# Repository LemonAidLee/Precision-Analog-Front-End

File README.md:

# Precision Mixed-Signal Data Acquisition Front End (AFE)

A four-stage precision analog front end that conditions a ±100 mV bipolar sensor signal into the 0–3.3 V unipolar window of a 16-bit ADS1115 ADC, designed for an ESP32-WROOM-32 host. Designed, simulated in LTspice, and laid out in KiCad. **Not built — no physical hardware exists.**

*Rev A board (78 mm × 100 mm, 2-layer), KiCad 3D render. The physical board has not been manufactured.*

---

## Overview

A sensor that outputs a few tens of millivolts, swinging both positive and negative, cannot be connected to a single-supply ADC. It is too small to use the converter's resolution, it goes below the converter's ground rail, and it carries out-of-band content the converter will alias.

This project is the hardware that sits between the two: an analog front end that band-limits, amplifies, and re-centres the signal so that a 16-bit ADC sees a well-conditioned, in-range voltage, and an ESP32 can read it over I²C.

| | |
|---|---|
| **Input** | ±100 mV bipolar, single-ended (J1) |
| **Output** | 0.31 V … 2.96 V unipolar, centred on VREF (to ADS1115 A0) |
| **Overall gain** | 13.25 V/V (22.4 dB) |
| **Bandwidth** | 2nd-order Butterworth low-pass, f₀ = 1.06 kHz |
| **Analog supply** | ±15 V (unregulated), external via screw terminal (J2); regulated on-board to ±12 V by LM7812 / LM7912 |
| **Digital supply** | 3.3 V from the ESP32 module's on-board regulator |
| **Op-amps** | 2 × TL082 (dual JFET-input), DIP-8 |
| **ADC** | ADS1115 breakout, 16-bit, I²C, ±4.096 V FSR |
| **Board** | 78 mm × 100 mm, 2-layer, 1.6 mm, all through-hole |
| **Status** | Designed · Simulated (DC) · Schematic complete · PCB fully routed with GND pour |

---

## Engineering motivation

Connecting a low-level sensor directly to a microcontroller ADC fails for four independent reasons, and each one needs its own circuit stage:

| Problem | Consequence | Stage that solves it |
|---|---|---|
| Signal is out-of-band above ~1 kHz | High-frequency interference folds back into the measurement band | Stage 1 — Sallen-Key low-pass |
| Signal is ~100 mV into a 4.096 V converter span | Only ~2.4 % of the ADC range is used; quantisation noise dominates | Stage 2 — ×10 gain |
| Signal is bipolar; the ADC ground rail is 0 V | Negative half-cycles are clipped or damage the input | Stage 3 — inverting summing level shift onto VREF |
| The summing stage inverts the signal | Polarity is wrong at the ADC | Stage 4 — unity-gain inverter |

Doing all four in one stage is possible but couples the design decisions together — the gain would set the filter Q, the offset would move with gain, and nothing could be probed independently. Splitting them keeps every design equation independent and gives four testable nodes.

---

## Signal flow

```
                 ±100 mV                  ±159 mV               ±1.59 V
   SENSOR ──▶ ┌───────────┐  VFILTER  ┌───────────┐  VAMP  ┌──────────────┐
   J1         │  STAGE 1  │ ────────▶ │  STAGE 2  │ ─────▶ │   STAGE 3    │
              │ Sallen-Key│           │ Non-inv.  │        │  Inverting   │
              │  LPF ×1.59│           │  amp ×10  │        │  summer      │
              │  U1A      │           │  U1B      │        │  U2A         │
              └───────────┘           └───────────┘        └──────┬───────┘
                                                                  │ VX
                        +3.3 V                                    │ −2.96 … −0.31 V
                          │                                       ▼
                     ┌────┴────┐  VREF = 1.637 V           ┌──────────────┐
                     │ 470/470 │ ─────────────────────────▶│   STAGE 4    │
                     │ divider │                           │ Unity inv.   │
                     │ + 100 nF│                           │  U2B         │
                     └─────────┘                           └──────┬───────┘
                                                                  │ VADC
                                                                  │ 0.31 … 2.96 V
                                                                  ▼
                                                        ┌────────────────────┐
                                                        │ ADS1115  (A0)      │
                                                        │ 16-bit, ±4.096 V   │
                                                        └─────────┬──────────┘
                                                                  │ I²C (SDA/SCL)
                                                                  ▼
                                                        ┌────────────────────┐
                                                        │ ESP32-WROOM-32     │
                                                        └────────────────────┘
```

Full node-by-node breakdown: **[03 — Signal Path](docs/03_Signal_Path.md)**

---

## Key specifications

| Parameter | Design value | Source |
|---|---|---|
| Input range | ±100 mV | Design target (silkscreened on board) |
| Stage 1 passband gain, K | 1 + 5.9k/10k = **1.590** | Calculated, LTspice-confirmed |
| Stage 1 cutoff, f₀ | 1/(2π·1.5k·100n) = **1061 Hz** | Calculated |
| Stage 1 Q | 1/(3 − K) = **0.709** (Butterworth ≈ 0.707) | Calculated |
| Stage 2 gain | 1 + 90k/10k = **10.00** | Calculated, LTspice-confirmed |
| Stage 3 signal gain | −30k/36k = **−0.8333** | Calculated, LTspice-confirmed |
| Stage 3 reference gain | −30k/30k = **−1.000** | Calculated |
| Stage 4 gain | −10k/10k = **−1.000** | Calculated |
| **Total gain, VSENSOR → VADC** | **13.25 V/V** | LTspice: 13.248 V/V |
| VREF (unloaded) | 3.3 × 470/940 = **1.650 V** | Calculated |
| VREF (loaded by Rref1) | **1.637 V** | LTspice: 1.6372 V |
| VADC at −100 mV / 0 / +100 mV | 0.313 / 1.637 / 2.962 V | LTspice (TL082) |
| ADC resolution referred to input | 4.096 V / 2¹⁵ / 13.25 = **9.4 µV/LSB** | Calculated |

---

## Hardware architecture

**Analog section** (left half of the board) — two TL082 dual op-amps in DIP-8 provide the four amplifier stages. All resistors are 1/4 W axial through-hole on a 10.16 mm pitch, arranged in a single labelled column so every feedback network can be identified and swapped without a schematic in hand. Analog supplies enter on a 3-pin 5 mm screw terminal (+15V_RAW / GND / −15V_RAW) from an external bench supply; on-board **LM7812 / LM7912 linear regulators** (U3/U4, with C4–C7 input/output bypass) clean this to the ±12 V the op-amps actually run on. The raw rail needs headroom above 12 V for the regulators to hold regulation, which is why the connector is no longer labelled ±12 V directly.

**Digital section** (right half) — the ESP32 dev board seats in two 1×19 pin sockets and supplies 3.3 V from its own regulator; the ADS1115 breakout seats in a 1×10 socket above it. The two sections meet only at the VADC trace and the shared ground.

Details: **[07 — KiCad Schematic and PCB](docs/07_KiCad_Schematic_and_PCB.md)**

---

## Simulation

Design verification was done in LTspice in two phases.

**Phase 1 — stage development with OP1177.** Each stage was designed, simulated, and iterated on its own bench: the Sallen-Key filter (AC sweep + transient), the ×10 gain stage (AC + transient), the level shifter, and then a two-stage and finally a four-stage integration. This phase used the OP1177 model that ships with LTspice, and produced the resistor values now in the schematic.

**Phase 2 — TL082 substitution.** The physical build targets TL082, so a third-party TL082 PSpice macromodel (`TL082.lib`) was brought in and the full chain re-run against it. The DC transfer at −100 mV / 0 / +100 mV was extracted and matches the ideal transfer function to within 0.02 %.

*Four-stage chain as simulated with the TL082 macromodel.*

| Test condition | Ideal (calculated) | LTspice, TL082 | Δ |
|---|---:|---:|---:|
| VSENSOR = 0 | 1.637 V | 1.63737 V | +0.4 mV |
| VSENSOR = +100 mV | 2.962 V | 2.96220 V | +0.2 mV |
| VSENSOR = −100 mV | 0.313 V | 0.31254 V | −0.2 mV |

**Two simulation issues are open and are not hidden here:** the TL082 build's filter section is wired as a passive two-pole RC rather than the Sallen-Key that is in the KiCad schematic (DC results unaffected, AC results not representative), and the OP1177 reference file no longer runs. Both are documented in **[05 — LTspice Simulation](docs/05_LTspice_Simulation.md)**.

Full detail: **[05 — LTspice Simulation](docs/05_LTspice_Simulation.md)** · **[06 — Simulation Results](docs/06_Simulation_Results.md)**

---

## PCB design

*F.Cu (red), B.Cu (blue — mostly the GND pour), silkscreen and board outline. Fully routed.*

- **78.1 mm × 99.6 mm** bounding box (2 layers, 1.6 mm FR4)
- 29 footprints, all through-hole; 115 pads
- 209 track segments (112 on F.Cu, 97 on B.Cu), ≈1355 mm total; 10 vias (0.6 mm / 0.3 mm drill)
- **GND poured on both F.Cu and B.Cu** (2 zones, 0.25 mm min thickness)
- Design rules: 0.2 mm min clearance, 0.2 mm min track, 0.5 mm copper-to-edge
- **DRC: 0 violations.** **ERC: 0 errors, 32 warnings** (all "label connected to only one pin" — the unused ESP32 GPIO breakout labels)
- No test points; no local decoupling at the op-amp supply pins

**Routing is complete.** Every net — including the seven internal analog nodes (the two filter nodes and the five op-amp inverting-input/feedback nodes) that an earlier netlist-sync bug had left with no copper — now has a fully routed connection, plus a GND pour on both layers. See **[07 — KiCad Schematic and PCB](docs/07_KiCad_Schematic_and_PCB.md)** for the routing table and the story of that bug.

---

## ESP32 + ADS1115 interface

The digital side is a **hardware interface only — no firmware has been written.**

| ADS1115 (J5) | Net | Goes to |
|---|---|---|
| 1 VDD | +3V3 | J3-1 (ESP32 3V3) |
| 2 GND | GND | Board ground |
| 3 SCL | SCL | J4-3 (ESP32 GPIO22) |
| 4 SDA | SDA | J4-6 (ESP32 GPIO21) |
| 5 ADDR | GND | Sets I²C address 0x48 |
| 6 ALRT | — | Not connected |
| 7 A0 | **VADC** | Stage 4 output |
| 8–10 A1–A3 | — | Not connected |

Details: **[09 — ESP32 + ADS1115 Interface](docs/09_ESP32_ADS1115_Interface.md)**

---

## Verification status

| Item | Designed | Simulated | On PCB | Routed | Physically tested |
|---|:--:|:--:|:--:|:--:|:--:|
| Sallen-Key low-pass (U1A) | ✓ | ✓ (AC/transient, OP1177 · DC only, TL082) | ✓ | ✓ | — |
| ×10 gain stage (U1B) | ✓ | ✓ (AC/transient, OP1177 · DC, TL082) | ✓ | ✓ | — |
| Level shifter (U2A) | ✓ | ✓ (DC, TL082) | ✓ | ✓ | — |
| Unity inverter (U2B) | ✓ | ✓ (DC, TL082) | ✓ | ✓ | — |
| 1.65 V reference divider | ✓ | ✓ (DC, TL082, incl. loading) | ✓ | ✓ | — |
| ADS1115 interface | ✓ | — | ✓ | ✓ | — |
| ESP32 interface | ✓ | — | ✓ | ✓ | — |
| ±12 V regulation (LM7812/LM7912) | ✓ | ideal sources only in signal-chain sims | ✓ | ✓ | — |
| Firmware | — | — | — | — | — |

**No physical prototype exists.** The board has not been fabricated, assembled, powered, or measured. Every performance figure in this repository is either a hand calculation or an LTspice result. Physical hardware validation is outside the current project scope.

---

## Engineering challenges

- **Choosing K = 1.59 rather than "gain = 1".** In an equal-component Sallen-Key, the passband gain and the pole Q are the same knob: Q = 1/(3 − K). A unity-gain buffer would give Q = 0.5 (overdamped, soft knee). K = 1.586 is the value that lands Q on 0.7071 — maximally flat. The 5.9 kΩ / 10 kΩ pair gives K = 1.590 and Q = 0.709, 0.3 % from ideal, using stock values.
- **Sizing the level shifter so the extremes stay inside the rail, not just the centre.** An earlier iteration used Rin1 = 20 kΩ. That still centred on 1.65 V at zero input, but the ±100 mV extremes landed at −0.74 V and +4.03 V — outside the ADC's supply rails in both directions. Rin1 = 36 kΩ trades gain for headroom and puts the extremes at 0.31 V / 2.96 V.
- **Predicting the reference divider's error before simulating it.** VREF is not 1.650 V in circuit; Rref1 (30 kΩ) sinks ~55 µA from a 235 Ω source, pulling it to 1.637 V. That 13 mV shift is a fixed offset the firmware can calibrate out — but it had to be identified as a systematic error rather than mistaken for simulation noise.
- **Migrating from a model that exists to a part that can be bought.** OP1177 has a vendor-supplied LTspice model; TL082 does not ship with LTspice. Getting the TL082 macromodel to converge required source stepping, and re-running the chain surfaced the fact that the two integration files had drifted apart.

---

## Current project status

**Designed · Simulated · Schematic complete · PCB placed and fully routed with a GND pour · Documented.**

Not manufactured, not assembled, not physically validated, not production-ready.

---

## Limitations

- No physical prototype; no oscilloscope, multimeter, or spectrum measurements of any kind.
- No local supply decoupling at the TL082 pins, no test points on the current board.
- ±12 V is regulated on-board (LM7812/LM7912), but the input rail is still an external, unregulated ±15 V supply — there is no AC-mains or USB-derived path to that rail.
- The TL082 full-chain simulation covers **DC only**; there is no AC or transient run against the TL082 model, and its filter section does not match the board.
- The AC and transient results in this repository were produced with **OP1177**, not the TL082 that is on the schematic.
- The 1.06 kHz filter corner sits above the ADS1115's 430 Hz Nyquist frequency at its 860 SPS maximum rate — it band-limits the signal but does not anti-alias the converter.
- No input protection, no reverse-polarity protection, no sensor characterisation.
- No firmware.

---

## Future improvements

1. Resolve the two open simulation discrepancies (filter topology in the TL082 file; repair the OP1177 reference bench).
2. Run AC and transient sweeps against the TL082 model and compare to the OP1177 reference.
3. Add 100 nF decoupling at each TL082 supply pin, and test points at VSENSOR / VFILTER / VAMP / VREF / VADC.
4. Fabricate and assemble; bring up the rails before the signal chain.
5. Measure DC transfer, frequency response, and noise floor; compare against simulation.
6. Write ESP32 firmware: I²C driver for the ADS1115, offset/gain calibration, data logging.
7. Revise to Rev B against measured data.

**Done since the last revision of this document:** PCB routing is complete (including seven internal analog nets a netlist-sync bug had silently left unrouted — see [07 §5](docs/07_KiCad_Schematic_and_PCB.md#5-resolution--the-unrouted-nets-and-the-bug-behind-them)), a GND pour was added on both copper layers, and on-board LM7812/LM7912 regulation replaced the external-±12V-only supply architecture.

---

## Repository structure

```
.
├── README.md                     ← this file
├── docs/                         ← full engineering documentation
│   ├── README.md                 ← documentation index
│   ├── 01_Project_Overview.md
│   ├── 02_System_Architecture.md
│   ├── 03_Signal_Path.md
│   ├── 04_Analog_Circuit_Design.md
│   ├── 05_LTspice_Simulation.md
│   ├── 06_Simulation_Results.md
│   ├── 07_KiCad_Schematic_and_PCB.md
│   ├── 08_Components_and_BOM.md
│   ├── 09_ESP32_ADS1115_Interface.md
│   ├── 10_Engineering_Decision.md
│   ├── Portfolio_Summary.md      ← recruiter-facing summary
│   ├── images/                   ← schematic, PCB and LTspice figures
│   └── design_files/             ← generated PDF / BOM exports + source pointers
├── KiCAD_PCB_Design/             ← KiCad 10 project (schematic, PCB, STEP)
├── LTSpice_Simulation/           ← LTspice schematics, netlists, TL082 model
└── Precision DAQ AFE_Documentation/   ← original engineering log / working notes
```

---

## Skills demonstrated

**Analog design** — active filter synthesis (Sallen-Key, Butterworth Q targeting), op-amp gain-stage design, inverting summing amplifiers, level shifting, resistive reference design with loading analysis, supply-rail headroom budgeting.

**Simulation** — LTspice AC / transient / DC-sweep analysis, third-party SPICE macromodel integration, convergence troubleshooting (Gmin and source stepping), model-substitution verification, netlist-level inspection.

**PCB design** — KiCad 10 schematic capture, footprint assignment, through-hole layout, functional block placement, analog/digital section separation, DRC/ERC.

**Mixed-signal / embedded** — external ADC selection and interfacing, I²C bus wiring, ADS1115 address strapping and PGA range selection, ESP32 dev-board integration.

**Engineering process** — requirement-driven stage decomposition, quantitative trade-off analysis, iterative design revision with superseded values preserved, honest separation of calculated / simulated / measured, self-audit of design-file consistency.

---

## Documentation

Start at **[docs/README.md](docs/README.md)** for the full index.

- **[docs/01–09](docs/README.md)** — the technical documentation: overview, architecture, signal path, circuit design, simulation, PCB, BOM, and the ESP32/ADS1115 interface.
- **[docs/10_Engineering_Decision.md](docs/10_Engineering_Decision.md)** — every significant design choice, the alternative it was taken over, and the reasoning.
- **[docs/Portfolio_Summary.md](docs/Portfolio_Summary.md)** — a short, recruiter-facing summary of the same project.

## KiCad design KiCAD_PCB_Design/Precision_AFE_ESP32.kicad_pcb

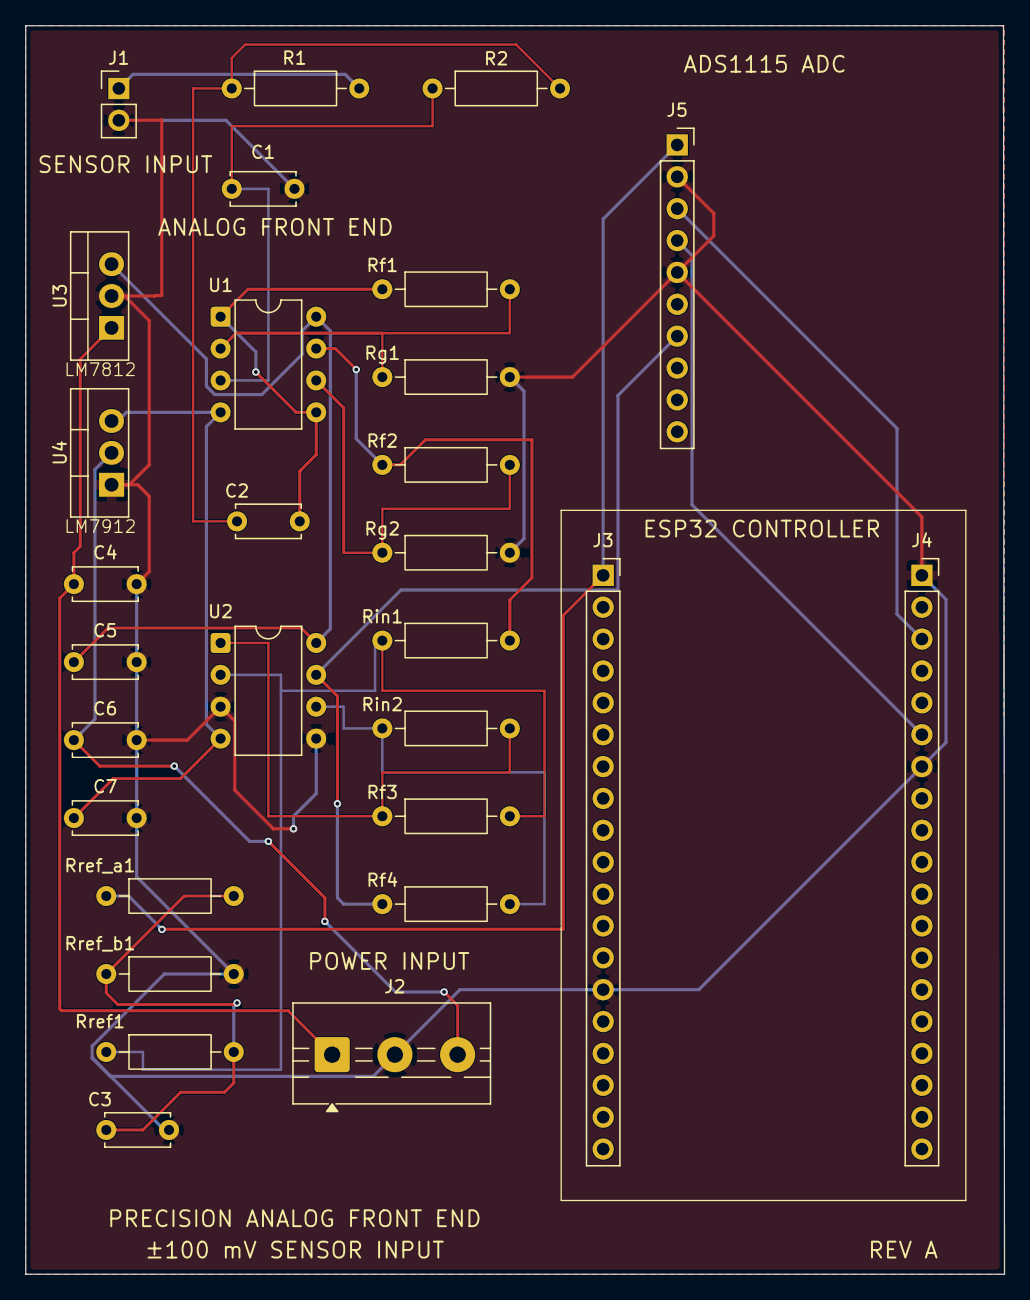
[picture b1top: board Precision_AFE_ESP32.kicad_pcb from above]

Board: 2 copper layers, 78.0 x 99.5 mm, 29 parts (0 on the bottom side), 20 nets.

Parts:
C1, C2, C3, C5, C7: 100n; C_Disc_D5.0mm_W2.5mm_P5.00mm
C4, C6: 330n; C_Disc_D5.0mm_W2.5mm_P5.00mm
J1: SENSOR_INPUT; PinHeader_1x02_P2.54mm_Vertical
J2: POWER_INPUT; TerminalBlock_MaiXu_MX126-5.0-03P_1x03_P5.00mm
J3: ESP32_LEFT_HDR; PinSocket_1x19_P2.54mm_Vertical
J4: ESP32_RIGHT_HDR; PinSocket_1x19_P2.54mm_Vertical
J5: ADS1115_MODULE; PinSocket_1x10_P2.54mm_Vertical
R1, R2: 1.5k; R_Axial_DIN0207_L6.3mm_D2.5mm_P10.16mm_Horizontal
Rf1: 5.9k; R_Axial_DIN0207_L6.3mm_D2.5mm_P10.16mm_Horizontal
Rf2: 90k; R_Axial_DIN0207_L6.3mm_D2.5mm_P10.16mm_Horizontal
Rf3: 30k; R_Axial_DIN0207_L6.3mm_D2.5mm_P10.16mm_Horizontal
Rf4: 10k; R_Axial_DIN0207_L6.3mm_D2.5mm_P10.16mm_Horizontal
Rg1, Rg2: 10k; R_Axial_DIN0207_L6.3mm_D2.5mm_P10.16mm_Horizontal
Rin1: 36k; R_Axial_DIN0207_L6.3mm_D2.5mm_P10.16mm_Horizontal
Rin2: 10k; R_Axial_DIN0207_L6.3mm_D2.5mm_P10.16mm_Horizontal
Rref1: 30k; R_Axial_DIN0207_L6.3mm_D2.5mm_P10.16mm_Horizontal
Rref_a1: 470; R_Axial_DIN0207_L6.3mm_D2.5mm_P10.16mm_Horizontal
Rref_b1: 470; R_Axial_DIN0207_L6.3mm_D2.5mm_P10.16mm_Horizontal
U1, U2: TL082; DIP-8_W7.62mm
U3: LM7812; TO-220-3_Vertical
U4: LM7912; TO-220-3_Vertical

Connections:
+3V3: J3.1, J5.1, Rref_a1.1
+12V: C5.1, U1.8, U2.8, U3.3 (VO)
+15V_RAW: C4.1, J2.1, U3.1 (VI)
-12V: C7.1, U1.4, U2.4, U4.3 (VO)
-15V_RAW: C6.1, J2.3, U4.2 (VI)
GND: C1.2, C3.2, C4.2, C5.2, C6.2, C7.2, J1.2, J2.2, J3.14, J4.1, J4.7, J5.2, J5.5, Rg1.2, Rg2.2, Rref_b1.2, U2.3, U2.5, U3.2 (GND), U4.1 (GND)
unnamed: C2.1, R1.1, R2.2
unnamed: Rf3.1, Rin2.2, U2.1
unnamed: C1.1, R2.1, U1.3
unnamed: Rf1.2, Rg1.1, U1.2
unnamed: Rf2.2, Rg2.1, U1.6
unnamed: Rf3.2, Rin1.1, Rref1.1, U2.2
unnamed: Rf4.2, Rin2.1, U2.6
SCL: J4.3, J5.3
SDA: J4.6, J5.4
VADC: J5.7, Rf4.1, U2.7
VAMP: Rf2.1, Rin1.2, U1.7
VFILTER: C2.2, Rf1.1, U1.1, U1.5
VREF: C3.1, Rref1.2, Rref_a1.2, Rref_b1.1
VSENSOR: J1.1, R1.2

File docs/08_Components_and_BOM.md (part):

# 08 — Components and BOM

[← Documentation index](README.md)

Read directly from `Precision_AFE_ESP32.kicad_sch` (Rev A). Machine-generated CSV: [`design_files/Precision_AFE_ESP32_bom.csv`](design_files/Precision_AFE_ESP32_bom.csv).

**29 placed components** (plus 4 `PWR_FLAG` schematic-only symbols), **115 pads**, **100 % through-hole**.

---

## Bill of materials, by function

### Input

| Ref | Component  | Value               | Footprint                           | Role                                     | Engineering rationale                                                                                           |
| --- | ---------- | ------------------- | ----------------------------------- | ---------------------------------------- | ------------------------------------------------------------------------------------------------------- |
| J1  | Pin header | SENSOR_INPUT, 1×02 | `PinHeader_1x02_P2.54mm_Vertical` | Sensor signal (pin 1) and return (pin 2) | 0.1 in header provides immediate compatibility with standard jumper wires for rapid prototype bring-up. |

### Stage 1 — Sallen-Key low-pass filter

| Ref | Component    | Value   | Footprint                                  | Role                                     | Engineering rationale                                                                                                      |
| --- | ------------ | ------- | ------------------------------------------ | ---------------------------------------- | ------------------------------------------------------------------------------------------------------------------- |
| R1  | Resistor     | 1.5 kΩ | `R_Axial_DIN0207_L6.3mm_D2.5mm_P10.16mm` | Filter series resistor                   | With C = 100 nF, establishes the precise f₀ = 1061 Hz target. Standard E24 value ensures immediate availability.                           |
| R2  | Resistor     | 1.5 kΩ | as above                                   | Filter series resistor                   | Equal-component design mathematically streamlines the Q and f₀ equations.                                                |
| C1  | Ceramic disc | 100 nF  | `C_Disc_D5.0mm_W2.5mm_P5.00mm`           | Shunt capacitor at the op-amp input node | Utilizes the most universal ceramic value; solving R relative to a fixed C ensures R remains in the optimal 1–10 kΩ range. |
| C2  | Ceramic disc | 100 nF  | as above                                   | Sallen-Key feedback capacitor            | Equal-component design mathematically requires C1 = C2.                                                                                   |
| Rf1 | Resistor     | 5.9 kΩ | Axial DIN0207                              | Sets passband gain K = 1.59              | The 5.9k/10k ratio hits K = 1.59, landing within an exceptional 0.25 % of the ideal Butterworth Q requirement.                                |
| Rg1 | Resistor     | 10 kΩ  | Axial DIN0207                              | Gain-setting leg to ground               | 10 kΩ optimally balances op-amp output loading against input bias-current error minimization.               |

### Stage 2 — ×10 amplifier

| Ref | Component | Value  | Footprint     | Role               | Engineering rationale                                                                                           |
| --- | --------- | ------ | ------------- | ------------------ | -------------------------------------------------------------------------------------------------------- |
| Rf2 | Resistor  | 90 kΩ | Axial DIN0207 | Feedback           | The 90k/10k ratio delivers exactly ×10 amplification. Sourcing from the same reel naturally cancels tolerance drift. |
| Rg2 | Resistor  | 10 kΩ | Axial DIN0207 | Gain leg to ground | Utilizes the standard 10 kΩ base.                                                                                         |

### Stage 3 — Level shifter (inverting summer)

| Ref   | Component | Value  | Footprint     | Role                            | Engineering rationale                                                                                                                                                         |
| ----- | --------- | ------ | ------------- | ------------------------------- | ---------------------------------------------------------------------------------------------------------------------------------------------------------------------- |
| Rin1  | Resistor  | 36 kΩ | Axial DIN0207 | Signal input to summing node    | The critical headroom-setting parameter. The 30k/36k = 0.833 scaling perfectly centers the output extremes at 0.31 / 2.96 V. |
| Rref1 | Resistor  | 30 kΩ | Axial DIN0207 | Reference input to summing node | Matches Rf3 to provide precise unity gain for the reference injection, guaranteeing VADC centers on VREF.                                                                                              |
| Rf3   | Resistor  | 30 kΩ | Axial DIN0207 | Summing-amplifier feedback      | Establishes the common scaling factor for the summing node.                                                                                                                                               |

### Stage 4 — Unity inverter

| Ref  | Component | Value  | Footprint     | Role              | Engineering rationale                                                        |
| ---- | --------- | ------ | ------------- | ----------------- | --------------------------------------------------------------------- |
| Rin2 | Resistor  | 10 kΩ | Axial DIN0207 | Inverter input    | Identical to Rf4; utilizing matched E96 pairs elegantly neutralizes tolerance error in the unity inversion. |
| Rf4  | Resistor  | 10 kΩ | Axial DIN0207 | Inverter feedback | Identical to Rin2.                                                              |

### Reference

| Ref     | Component    | Value  | Footprint                        | Role                          | Engineering rationale                                                                                   |
| ------- | ------------ | ------ | -------------------------------- | ----------------------------- | ------------------------------------------------------------------------------------------------ |
| Rref_a1 | Resistor     | 470 Ω | Axial DIN0207                    | Upper divider leg from +3.3 V | The aggressive 470 Ω value limits Thévenin source impedance to 235 Ω, intelligently suppressing loading error to just 13 mV.            |
| Rref_b1 | Resistor     | 470 Ω | Axial DIN0207                    | Lower divider leg to GND      | Matched to Rref_a1 to provide an exact halving of the rail.                                                        |
| C3      | Ceramic disc | 100 nF | `C_Disc_D5.0mm_W2.5mm_P5.00mm` | Reference bypass              | Standard bulk decoupling to shunt high-frequency rail noise from the critical VREF node to ground. |

### Active devices

| Ref | Component    | Value | Footprint                     | Role                               | Engineering rationale                                                                                                                      |
| --- | ------------ | ----- | ----------------------------- | ---------------------------------- | ---------------------------------------------------------------------------------------------------------------------------------- |
| U1  | Op-amp, dual | TL082 | `Package_DIP:DIP-8_W7.62mm` | Unit A = Stage 1, unit B = Stage 2 | Precision JFET input guarantees negligible bias current into the high-impedance feedback networks. Sourced in DIP-8 for rapid prototype socketing. |
| U2  | Op-amp, dual | TL082 | `Package_DIP:DIP-8_W7.62mm` | Unit A = Stage 3, unit B = Stage 4 | Leverages the dual package to execute the complete signal chain across only two ICs.                                                                                               |

### Power input
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
